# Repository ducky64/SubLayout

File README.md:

# SubLayout
KiCad plugin to merge (or create) a sub-pcb-layout into (or from) a top-level board, following the hierarchical sheet structure of the board. Compatible with schematic-less (netlist import) flows that encode hierarchical tstamp data.

Tested compatible with KiCad 8 and 10. Zone replication is broken on KiCad 10 due to plugin API changes.

KiCad 10 introduces native [design blocks](https://docs.kicad.org/10.0/en/pcbnew/pcbnew.html#pcb-design-blocks), which this plugin largely replicates.
This plugin may still be useful for schematic-less (netlist import) design flows, since the design blocks workflow is smoothest with schematic integration.
This also provides a lightweight interface that works with individual sublayout .kicad_pcb files, without needing the heavyweight design blocks library machinery.

Inspired by [SaveRestoreLayout](https://github.com/MitjaNemec/SaveRestoreLayout) and [HierarchicalPcb](https://github.com/gauravmm/HierarchicalPcb), but this plugin only uses the board layout file and does not require a schematic or any project structure.

<table>
<tr>
<td><b>Select anchor footprint ...</b>

</td>
<td><b>... invoke plugin ...</b>

</td>
<td><b>... profit</b>

</td>
</tr>

<tr>
<td/>
<td/>

<td><b>... or save sublayout</b>

as an editable .kicad_pcb file, restore-able to another board

</td>

</tr>
</table>

## Features
- Select and save the layout of a hierarchical block to a .kicad_pcb file.
  - Selection includes traces, vias, and zones of internal nets.
  - Selection expands to layout groups enclosing the footprints.
  - This file can be edited.
- Restore a saved layout to a hierarchical block of a board.
  - This includes footprint positions, traces, vias, and zones.
  - Optionally delete existing internal traces and groups (if applicable) before restoring
- Replicate a layout of a hierarchical block to other instances of that block in the same board. 
- Flexible matching by either hierarchical tstamp (component unique IDs) or relative refdes. 
  - Best-effort restore when the footprints or netlists do not match, allowing partial restores when the hierarhical sheet schematic has changed.

## Workflow
1. Select ONE anchor footprint.
   - Saving: select any footprint in the hierarchical block to be saved.
   - Restoring: select the footprint in the hierarchical block where the layout will be restored around.
   - Replicating: select the footprint of the source hierarchical block corresponding to the footprints of the instances where the layouts will be replicated around.
2. Invoke the plugin from the plugin menu or toolbar.
3. If needed, change the level of hierarchy to operate on.
   By default, the lowest (leaf-most) hierarchical block is selected.
4. Optionally, select multiple instances of the hierarchical block to replicate or restore.
5. Click 'Save', 'Replicate' or 'Restore' to perform the operation.

## Installation
_TODO: make available on the KiCad plugin / package manager_

Clone this repository into your KiCad plugins directory.
- On Windows, this is typically `C:\Users\<username>\Documents\KiCad\8.0\scripting\plugins`, and if cloned correctly, this file should exist: `C:\Users\<username>\Documents\KiCad\8.0\scripting\plugins\SubLayout\plugin.py`.

## Board Requirements
- Sublayouts work on hierarchical sheets.
  - For non-schematic flows (e.g., hardware description language to netlist to layout), netlists must encode hierarchy in footprint tstamp (component unique id) data and provide Sheetfile and Sheetname.
- In tstamp mode: component unique IDs must match when restoring or replicating sublayouts.
  - For non-schematic flows, this means footprint tstamp data must match.
- Alternatively, in refdes mode: relative component reference designators are used to match components between instances.
- Sheetname inference may fail if there are hierarchical sheets with no direct footprints.
  This may result in not finding other instances of a hierarhical sheet and is a limitation of the data available in the board layout file.

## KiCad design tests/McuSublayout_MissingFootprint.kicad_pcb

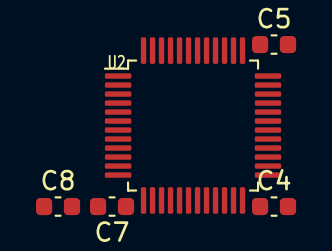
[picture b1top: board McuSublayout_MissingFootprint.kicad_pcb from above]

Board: 2 copper layers, 5 parts (0 on the bottom side), 2 nets, no tracks yet.

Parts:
C4, C5: 50V 100nF X7R ±10% 0603 Multilayer Ceramic Capaci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; C_0603_1608Metric
C7: 50V 10nF X7R ±10% 0603 Multilayer Ceramic Capacit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; C_0603_1608Metric
C8: 50V 1uF X5R ±10% 0603 Multilayer Ceramic Capacito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; C_0603_1608Metric
U2: STM32F103xxT6; LQFP-48_7x7mm_P0.5mm

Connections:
reg.pwr_out: C4.1, C5.1, C7.1, C8.1, U2.1, U2.9, U2.24, U2.36, U2.48
usb.gnd: C4.2, C5.2, C7.2, C8.2, U2.8, U2.23, U2.35, U2.44, U2.47

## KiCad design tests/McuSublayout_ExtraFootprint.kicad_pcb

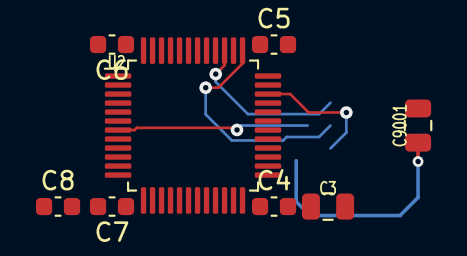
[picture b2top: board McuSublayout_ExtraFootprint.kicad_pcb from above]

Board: 2 copper layers, 9 parts (1 on the bottom side), 6 nets.

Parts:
C3, C9001: 25V 4.7uF X5R ±10% 0805 Multilayer Ceramic Capaci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; C_0805_2012Metric
C4, C5, C6: 50V 100nF X7R ±10% 0603 Multilayer Ceramic Capaci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; C_0603_1608Metric
C7: 50V 10nF X7R ±10% 0603 Multilayer Ceramic Capacit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; C_0603_1608Metric
C8: 50V 1uF X5R ±10% 0603 Multilayer Ceramic Capacito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; C_0603_1608Metric
J2: PinHeader1.27 Shrouded 2x5; PinHeader_2x05_P1.27mm_Vertical_SMD
U2: STM32F103xxT6; LQFP-48_7x7mm_P0.5mm

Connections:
extra: C9001.1, J2.7
mcu.reset_node: J2.10, U2.7
mcu.swd_node.swclk: J2.4, U2.37
mcu.swd_node.swdio: J2.2, U2.34
reg.pwr_out: C3.1, C4.1, C5.1, C6.1, C7.1, C8.1, J2.1, U2.1, U2.9, U2.24, U2.36, U2.48
usb.gnd: C3.2, C4.2, C5.2, C6.2, C7.2, C8.2, C9001.2, J2.3, J2.5, J2.9, U2.8, U2.23, U2.35, U2.44, U2.47

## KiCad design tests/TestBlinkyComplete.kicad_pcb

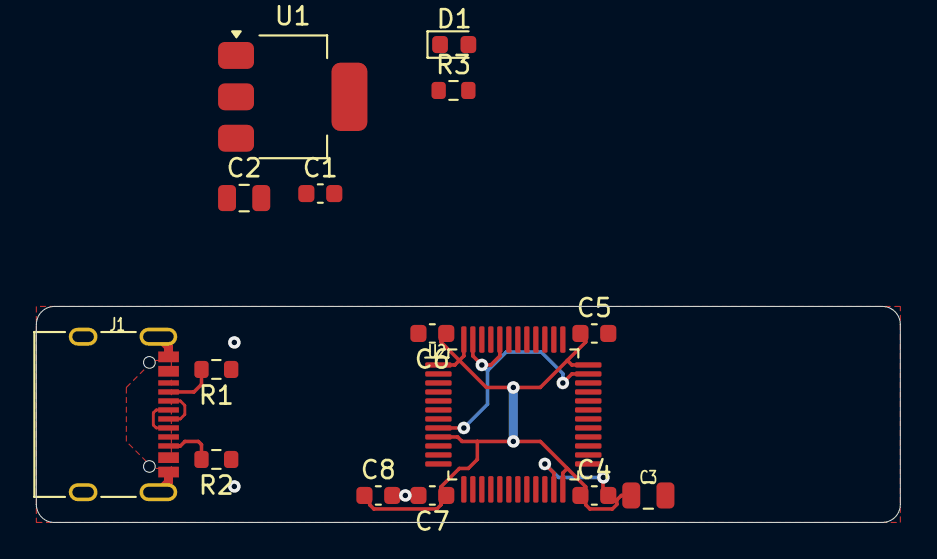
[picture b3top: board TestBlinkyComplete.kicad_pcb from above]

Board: 2 copper layers, 48.0 x 12.0 mm, 16 parts (1 on the bottom side), 12 nets.

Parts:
C1, C4, C5, C6: 50V 100nF X7R ±10% 0603 Multilayer Ceramic Capaci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; C_0603_1608Metric
C2: X5R 25V ±10% 10uF 0805 Multilayer Ceramic Capacit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; C_0805_2012Metric
C3: 25V 4.7uF X5R ±10% 0805 Multilayer Ceramic Capaci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; C_0805_2012Metric
C7: 50V 10nF X7R ±10% 0603 Multilayer Ceramic Capacit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; C_0603_1608Metric
C8: 50V 1uF X5R ±10% 0603 Multilayer Ceramic Capacito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; C_0603_1608Metric
D1: Red 615~630nm 1.9~2.2V 0603 Light Emitting Diodes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; LED_0603_1608Metric
J1: COM-15111; USB_C_Receptacle_XKB_U262-16XN-4BVC11
J2: PinHeader1.27 Shrouded 2x5; PinHeader_2x05_P1.27mm_Vertical_SMD
R1, R2, R3: ±1% 1/10W Thick Film Resistors 75V ±100ppm/? -55?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; R_0603_1608Metric
U1: LD1117S33TR; SOT-223-3_TabPin2
U2: STM32F103xxT6; LQFP-48_7x7mm_P0.5mm

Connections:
led.res.a: D1.1, R3.1
led.signal: D1.2, U2.10
mcu.reset_node: J2.10, U2.7
mcu.swd_node.swclk: J2.4, U2.37
mcu.swd_node.swdio: J2.2, U2.34
reg.pwr_out: C2.1, C3.1, C4.1, C5.1, C6.1, C7.1, C8.1, J2.1, U1.2, U2.1, U2.9, U2.24, U2.36, U2.48
usb.conn.cc.cc1: J1.A5, R1.2
usb.conn.cc.cc2: J1.B5, R2.2
usb.gnd: C1.2, C2.2, C3.2, C4.2, C5.2, C6.2, C7.2, C8.2, J1.A1, J1.A12, J1.B1, J1.B12, J1.S1, J2.3, J2.5, J2.9, R1.1, R2.1, R3.2, U1.1, U2.8, U2.23, U2.35, U2.44, U2.47
usb.pwr: C1.1, J1.A4, J1.A9, J1.B4, J1.B9, U1.3
usb.usb.dm: J1.A7, J1.B7
usb.usb.dp: J1.A6, J1.B6

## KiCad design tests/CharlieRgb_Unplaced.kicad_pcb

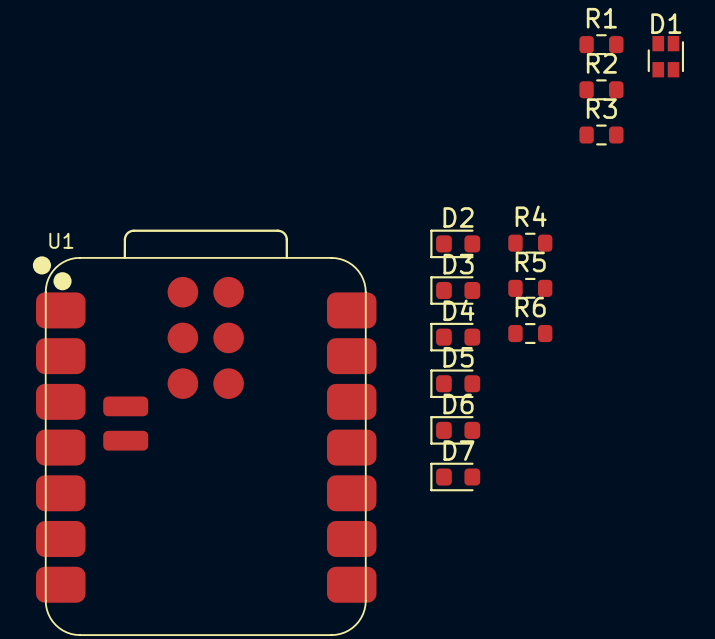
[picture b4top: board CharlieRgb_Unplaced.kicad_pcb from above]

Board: 2 copper layers, 14 parts (0 on the bottom side), 13 nets, no tracks yet.

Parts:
D1: EAST1616RGBB2; LED_LiteOn_LTST-C19HE1WT
D2, D3, D4, D5, D6, D7: Red 615~630nm 1.9~2.2V 0603 Light Emitting Diodes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; LED_0603_1608Metric
R1, R2, R3, R4, R5, R6: ±1% 1/10W Thick Film Resistors 75V ±100ppm/℃ -55℃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; R_0603_1608Metric
U1: XIAO ESP32C3; XIAO-ESP32C3-SMD

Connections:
CharlieplexedLedMatrix.led[0_0].k: D2.1, D3.1, R4.1
CharlieplexedLedMatrix.led[0_1].k: D4.1, D5.1, R5.1
CharlieplexedLedMatrix.led[0_2].k: D6.1, D7.1, R6.1
IndicatorSinkRgbLed.blue_res.a: D1.1, R3.1
IndicatorSinkRgbLed.green_res.a: D1.4, R2.1
IndicatorSinkRgbLed.pwr: D1.2, U1.12
IndicatorSinkRgbLed.red_res.a: D1.3, R1.1
IndicatorSinkRgbLed.signals.blue: R3.2, U1.4
IndicatorSinkRgbLed.signals.green: R2.2, U1.3
IndicatorSinkRgbLed.signals.red: R1.2, U1.2
Xiao_Esp32c3.gpio.gpio_14_0: D4.2, D6.2, R4.2, U1.5
Xiao_Esp32c3.gpio.gpio_14_1: D2.2, D7.2, R5.2, U1.6
Xiao_Esp32c3.gpio.gpio_14_2: D3.2, D5.2, R6.2, U1.11

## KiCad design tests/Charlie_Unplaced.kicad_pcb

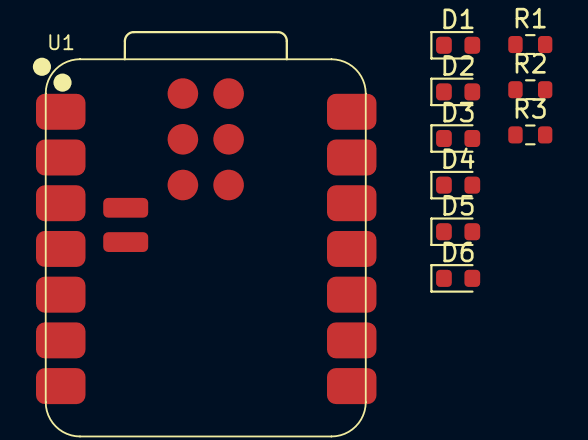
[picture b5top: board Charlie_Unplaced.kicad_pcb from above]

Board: 2 copper layers, 10 parts (0 on the bottom side), 6 nets, no tracks yet.

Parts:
D1, D2, D3, D4, D5, D6: Red 615~630nm 1.9~2.2V 0603 Light Emitting Diodes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; LED_0603_1608Metric
R1, R2, R3: ±1% 1/10W Thick Film Resistors 75V ±100ppm/℃ -55℃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; R_0603_1608Metric
U1: XIAO ESP32C3; XIAO-ESP32C3-SMD

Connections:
CharlieplexedLedMatrix.led[0_0].k: D1.1, D2.1, R1.1
CharlieplexedLedMatrix.led[0_1].k: D3.1, D4.1, R2.1
CharlieplexedLedMatrix.led[0_2].k: D5.1, D6.1, R3.1
Xiao_Esp32c3.gpio.gpio_14_0: D3.2, D5.2, R1.2, U1.2
Xiao_Esp32c3.gpio.gpio_14_1: D1.2, D6.2, R2.2, U1.3
Xiao_Esp32c3.gpio.gpio_14_2: D2.2, D4.2, R3.2, U1.4

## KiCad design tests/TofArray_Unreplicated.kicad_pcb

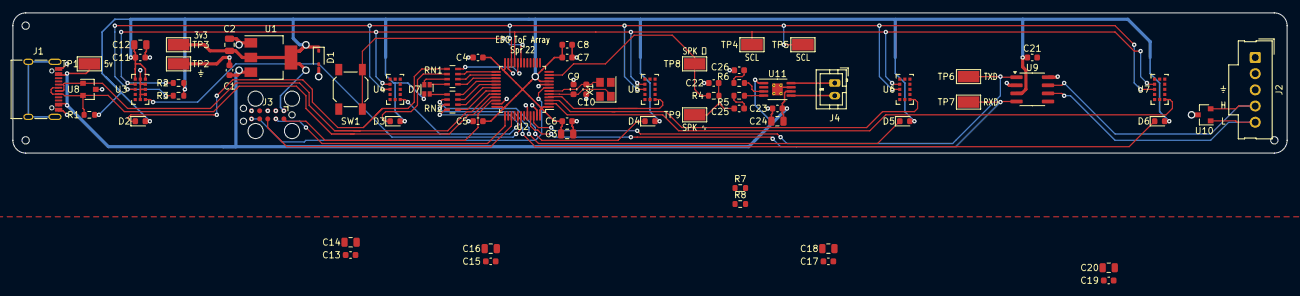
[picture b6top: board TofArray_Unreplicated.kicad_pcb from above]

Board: 2 copper layers, 200.0 x 22.0 mm, 72 parts (0 on the bottom side), 49 nets.

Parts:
C1, C4, C5, C6, C11, C13, C15, C17, C19, C21, C23: 50V 100nF X7R ±10% 0603 Multilayer Ceramic Capaci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; C_0603_1608Metric
C2, C3, C12, C14, C16, C18, C20, C24: 25V 4.7uF X5R ±10% 0805 Multilayer Ceramic Capaci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; C_0805_2012Metric
C7: 50V 10nF X7R ±10% 0603 Multilayer Ceramic Capacit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; C_0603_1608Metric
C8, C25, C26: 50V 1uF X5R ±10% 0603 Multilayer Ceramic Capacito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; C_0603_1608Metric
C9, C10: 50V 33pF C0G ±5% 0603 Multilayer Ceramic Capacito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; C_0603_1608Metric
C22: 50V 47nF X7R ±10% 0603 Multilayer Ceramic Capacit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; C_0603_1608Metric
D1: 5μA@1V 90Ω Single 3.53V~3.67V 200mW 3.6V SOD-323 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; D_SOD-323
D2, D3, D4, D5, D6: Red 615~630nm 1.9~2.2V 0603 Light Emitting Diodes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; LED_0603_1608Metric
D7: EAST1616RGBB2; LED_LiteOn_LTST-C19HE1WT
H1, H2, H3: JlcToolingHole_1.152mm
J1: COM-15111; USB_C_Receptacle_XKB_U262-16XN-4BVC11
J2: 171971-0005_1x05; Molex_SL_171971-0005_1x05_P2.54mm_Vertical
J3: Tag-Connect_TC2050-IDC-FP_2x05_P1.27mm_Vertical
J4: B2B-PH-K; JST_PH_B2B-PH-K_1x02_P2.00mm_Vertical
R1, R2, R3, R4, R5, R6, R7, R8: ±1% 1/10W Thick Film Resistors 75V ±100ppm/℃ -55℃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; R_0603_1608Metric
RN1, RN2: 4 ±5% 8 1kΩ 1/16W ±200ppm/℃ 1206 Resistor Network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; R_Array_Concave_4x0603
SW1: 5.1mm switch; SW_SPST_SKQG_WithoutStem
TP1: vusb; TestPoint_Keystone_5015_Micro-Minature
TP2: gnd; TestPoint_Keystone_5015_Micro-Minature
TP3: v3v3; TestPoint_Keystone_5015_Micro-Minature
TP4: i2c_chain_0.scl; TestPoint_Keystone_5015_Micro-Minature
TP5: i2c_chain_0.sda; TestPoint_Keystone_5015_Micro-Minature
TP6: can_chain_0.txd; TestPoint_Keystone_5015_Micro-Minature
TP7: can_chain_0.rxd; TestPoint_Keystone_5015_Micro-Minature
TP8: spk_chain_0; TestPoint_Keystone_5015_Micro-Minature
TP9: spk_chain_1; TestPoint_Keystone_5015_Micro-Minature
U1: LDL1117S33R; SOT-223-3_TabPin2
U2: STM32F103xxT6; LQFP-48_7x7mm_P0.5mm
U3, U4, U5, U6, U7: VL53L0X; ST_VL53L0X
U8: PESD5V0X1BT; SOT-23
U9: SN65HVD230DR; SOIC-8_3.9x4.9mm_P1.27mm
U10: PESD1CAN,215; SOT-23
U11: TPA2005D1; MSOP-8-1EP_3x3mm_P0.65mm_EP1.68x1.88mm_ThermalVias
X1: 12MHz SMD Crystal Resonator 20pF ±10ppm ±30ppm -4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; Crystal_SMD_3225-4Pin_3.2x2.5mm

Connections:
can_chain_0.rxd: TP7.1, U2.45, U9.4
can_chain_0.txd: TP6.1, U2.46, U9.1
can_chain_1.canh: J2.4, U9.7, U10.2
can_chain_1.canl: J2.5, U9.6, U10.1
gnd: C1.2, C2.2, C3.2, C4.2, C5.2, C6.2, C7.2, C8.2, C9.2, C10.2, C11.2, C12.2, C13.2, C14.2, C15.2, C16.2, C17.2, C18.2, C19.2, C20.2, C21.2, C22.2, C23.2, C24.2, C26.2, D1.2, J1.A1, J1.A12, J1.B1, J1.B12, J1.S1, J2.3, J3.2, J3.3, J3.5, R1.1, R2.1, SW1.2, TP2.1, U1.1, U2.8, U2.23, U2.35, U2.44, U2.47, U3.2, U3.3, U3.4, U3.6, U3.12, U4.2, U4.3, U4.4, U4.6, U4.12, U5.2, U5.3, U5.4, U5.6, U5.12, U6.2, U6.3, U6.4, U6.6, U6.12, U7.2, U7.3, U7.4, U7.6, U7.12, U8.3, U9.2, U9.8, U10.3, U11.7, U11.9, X1.2, X1.4
i2c_chain_0.scl: R4.2, TP4.1, U2.21, U3.10, U4.10, U5.10, U6.10, U7.10
i2c_chain_0.sda: R5.2, TP5.1, U2.22, U3.9, U4.9, U5.9, U6.9, U7.9
leds_chain_0.0: RN1.8, U2.20
leds_chain_0.1: RN1.7, U2.25
leds_chain_0.2: RN2.7, U2.29
leds_chain_0.3: RN2.6, U2.30
leds_chain_0.4: RN2.5, U2.31
leds_chain_0.5: RN1.6, U2.26
leds_chain_0.6: RN1.5, U2.27
leds_chain_0.7: RN2.8, U2.28
mcu.gpio.tof_reset_0: U2.42, U3.5
mcu.gpio.tof_reset_1: U2.41, U4.5
mcu.gpio.tof_reset_2: U2.4, U5.5
mcu.gpio.tof_reset_3: U2.3, U6.5
mcu.gpio.tof_reset_4: U2.2, U7.5
mcu.reset_node: J3.6, U2.7
mcu.swd.swo: J3.8, U2.39
mcu.swd_node.swclk: J3.9, U2.37
mcu.swd_node.swdio: J3.10, U2.34
mcu.xtal_node.xi: C9.1, U2.5, X1.1
mcu.xtal_node.xo: C10.1, U2.6, X1.3
res1.a.0: D2.1, RN1.1
res1.a.1: D3.1, RN1.2
res1.a.2: D7.3, RN1.3
res1.a.3: D7.4, RN1.4
res2.a.0: D7.1, RN2.1
res2.a.1: D4.1, RN2.2
res2.a.2: D5.1, RN2.3
res2.a.3: D6.1, RN2.4
spk_chain_0: R6.1, TP8.1, U2.11
spk_chain_1: C22.1, C25.2, R6.2, TP9.1
spk_chain_2.a: J4.1, U11.8
spk_chain_2.b: J4.2, U11.5
spk_drv.inn_cap.pos: C26.1, R8.1
spk_drv.inn_res.b: R8.2, U11.3
spk_drv.inp_cap.pos: C25.1, R7.1
spk_drv.inp_res.b: R7.2, U11.4
sw1_chain_0: SW1.1, U2.19
usb.conn.cc.cc1: J1.A5, R1.2
usb.conn.cc.cc2: J1.B5, R2.2
usb_chain_0.d_N: J1.A7, J1.B7, U2.32, U8.1
usb_chain_0.d_P: J1.A6, J1.B6, R3.2, U2.33, U8.2
v3v3: C2.1, C3.1, C4.1, C5.1, C6.1, C7.1, C8.1, C11.1, C12.1, C13.1, C14.1, C15.1, C16.1, C17.1, C18.1, C19.1, C20.1, C21.1, D1.1, D2.2, D3.2, D4.2, D5.2, D6.2, D7.2, J3.1, R3.1, R4.1, R5.1, TP3.1, U1.2, U2.1, U2.9, U2.24, U2.36, U2.48, U3.1, U3.11, U4.1, U4.11, U5.1, U5.11, U6.1, U6.11, U7.1, U7.11, U9.3
vusb: C1.1, C23.1, C24.1, J1.A4, J1.A9, J1.B4, J1.B9, TP1.1, U1.3, U11.1, U11.6

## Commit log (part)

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2025-04-14 Skeleton code
2025-04-14 bits and pieces
2025-04-14 compute sheetnames / files from path
2025-04-16 Highlight hierarchy
2025-04-16 refactoring
2025-04-17 test skeleton
2025-04-17 cleaning
2025-04-17 skeleton and formatting
2025-04-18 namer util class
2025-04-18 quick and dirty save test case
2025-04-18 more save filtering
2025-04-18 smarter net filter
2025-04-19 refactor to be a bit more functional
2025-04-19 wip replication skeleton
2025-04-19 wip preparation for replication testing
2025-04-19 wip correspondences
2025-04-19 complete correspondences code
2025-04-20 wip replication broken
2025-04-20 restoring
2025-04-20 replicate tracks
2025-04-20 support zones
2025-04-20 wip cleaning and refactoring and toplevel ui
2025-04-20 restructure
2025-04-20 cleaning tests
2025-04-20 dealias
2025-04-20 plumbing restore through
2025-04-20 cleanup zone behavior
2025-05-03 clean types
2025-05-04 WIP group-aware save and group utils
2025-05-07 red tests
2025-05-08 group tools
2025-05-08 tree lca algo w/ test
2025-05-08 not robust test cases
2025-05-09 wip group replication algo
2025-05-09 highest covering group
2025-05-09 wip groupaware filter op
2025-05-09 group-aware filter skeleton
2025-05-11 preserve group structure on save
2025-05-11 selection preview
2025-05-11 renaming
2025-05-11 deletion test
2025-05-11 replicate algo outline
2025-05-17 wip untested new correspondences structure
2025-05-17 tests r broken
2025-05-17 new correspondence code w/ tests
2025-05-17 untested position transform
2025-05-17 identity transform test
2025-05-17 (broken) rotate / flip tests
2025-05-18 fix rotation test cases
2025-05-18 target non-flipped fixed
2025-05-18 test all the things
2025-05-18 wip replication
2025-05-18 replicate w/ groups working kinda
2025-05-18 fix crashy bug
2025-05-18 almost there
2025-05-19 purge lca
2025-05-19 done?
2025-05-19 plumb things through
2025-05-19 fix checkbox functionality
2025-05-19 flip tracks
2025-05-19 proper handling of layers
2025-05-25 replicate track netcodes and store errors
2025-05-25 error case tests
2025-05-25 propagate warnings through ui
2025-05-26 Better error infra
2025-05-28 multi-instance test case
2025-05-28 wip multi-restore / replicate ui
2025-05-29 wip top level multi replicate
2025-05-29 support for replication
2025-05-29 replicate working
2025-06-01 wip light restructuring
2025-06-02 unit test for correspondence
2025-06-02 unit tests
2025-06-02 fix top level
2025-06-03 better docs
2025-06-22 test cases
2025-06-22 Add CharlieRgb test case
2025-06-22 match by refdes + tests
2025-06-22 tests passing
2025-06-22 plumb through toggles
2025-06-22 broken test =(
2025-06-22 implement esc closure
2025-06-22 Add option to match by relative refdes (#1)
    Matching on relative refdes allows loading a sub-layout into a board
    where they do not share the same schematic, for example if the
    sub-layout is from a layout generator that does not have tstamps.
    This is now the default (consistent with netlist import behavior), but
    the previous by-tstamp is available as an option.
    In replicate, changes internal indexing to by-refdes since the path is
2025-06-27 Better initial directory detection
2025-06-27 Restore last position
2025-07-22 Fix highlight-on-replicate
2026-06-25 Kinda KiCad10.0 compatibility
2026-06-25 Natural sorting by refdes
2026-06-27 group wrapper
    because the new group api is broken
2026-06-27 fixes
2026-06-27 workarounds
2026-06-27 fix bugs
2026-06-27 fixes for Kicad10
2026-06-27 Kicad 10 fixes (#2)
    Kicad 10 breaks a ton of APIs, most notably PCB_GROUP -> EDA_GROUP
    (which has a broken GetItems()) and removal of Zone APIs.
    This adds .items() into GroupWrapper, changes most group access to
    instantiate a GroupWrapper, and plumbs through the fallout.
    Zone replication is broken in Kicad 10.
    This is a stopgap / hack fix at best. This needs to be written for the
2026-06-27 Use existing split-refdes algo
2026-06-27 Cleanup and publishing script
2026-06-27 Add icon
2026-06-27 try again
2026-06-27 Fix publishing scripts
2026-06-27 Move tests to separate directory
2026-06-27 Clean release script
2026-06-27 Fix resources directory
2026-06-28 Remove download url from in-package metadata
2026-06-28 Move icon svg out of resources
